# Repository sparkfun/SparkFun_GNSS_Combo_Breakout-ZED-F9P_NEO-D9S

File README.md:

# SparkFun u-blox ZED-F9P NEO-D9S Combo Breakout

<p align="center">

</p>

*[SparkFun u-blox ZED-F9P NEO-D9S Combo Breakout (GPS-22560)](https://www.sparkfun.com/products/22560)*

The [SparkFun u-blox ZED-F9P NEO-D9S Combo Breakout (GPS-22560)](https://www.sparkfun.com/products/22560) combines the u-blox ZED-F9P multi-band high precision GNSS module with the NEO-D9S L-band GNSS correction data receiver. With a clear view of the sky, especially a clear view to the South, this combo breakout will deliver centimeter-level accuracy positioning without needing separate RTK or NTRIP corrections.

The Combo Breakout is designed to work with u-blox's PointPerfect L-band satellite GNSS augmentation service, which provides homogeneous coverage in contiguous USA.

### Important Note:

u-blox provides products and services to "B2B Customers". Only business customers are eligible to register for a Thingstream (PointPerfect) account. You may be required to demonstrate that the use of the combo breakout is in relation to your trade, business, craft or profession. u-blox products and services are not intended for individual consumer use.

## Repository Contents

* **[/docs](/docs/)** - Online documentation files
    * [board_files](/docs/assets/board_files/) - Files for the product design
        * [Eagle design files](https://github.com/sparkfun/SparkFun_GNSS_Combo_Breakout-ZED-F9P_NEO-D9S/blob/main/docs/assets/board_files/ZED-F9P_NEO-D9S_Combo_x02.zip) (.zip)
        * [Schematic](https://github.com/sparkfun/SparkFun_GNSS_Combo_Breakout-ZED-F9P_NEO-D9S/blob/main/docs/assets/board_files/SparkFun_GNSS_Combo_Breakout-ZED-F9P_NEO-D9S_Schematic.pdf) (.pdf)
        * [Dimensions](https://github.com/sparkfun/SparkFun_GNSS_Combo_Breakout-ZED-F9P_NEO-D9S/blob/main/docs/assets/board_files/SparkFun_GNSS_Combo_Breakout-ZED-F9P_NEO-D9S_Dimensions.png) (.png)
* **[/Hardware](/Hardware/)** - Eagle design files (.brd, .sch)

## Documentation

* **[Hookup Guide (mkdocs)](http://docs.sparkfun.com/SparkFun_GNSS_Combo_Breakout-ZED-F9P_NEO-D9S/)** - Hookup guide for the SparkFun u-blox ZED-F9P NEO-D9S Combo Breakout hosted by GitHub pages.

## Product Versions

* [GPS-22560](https://www.sparkfun.com/products/22560) - Initial SparkFun Release

## License Information

This product is _**open source**_! 

Please review the LICENSE.md file for license information. 

If you have any questions or concerns on licensing, please contact technical support on our [SparkFun forums](https://forum.sparkfun.com/viewforum.php?f=152).

Distributed as-is; no warranty is given.

- Your friends at SparkFun.

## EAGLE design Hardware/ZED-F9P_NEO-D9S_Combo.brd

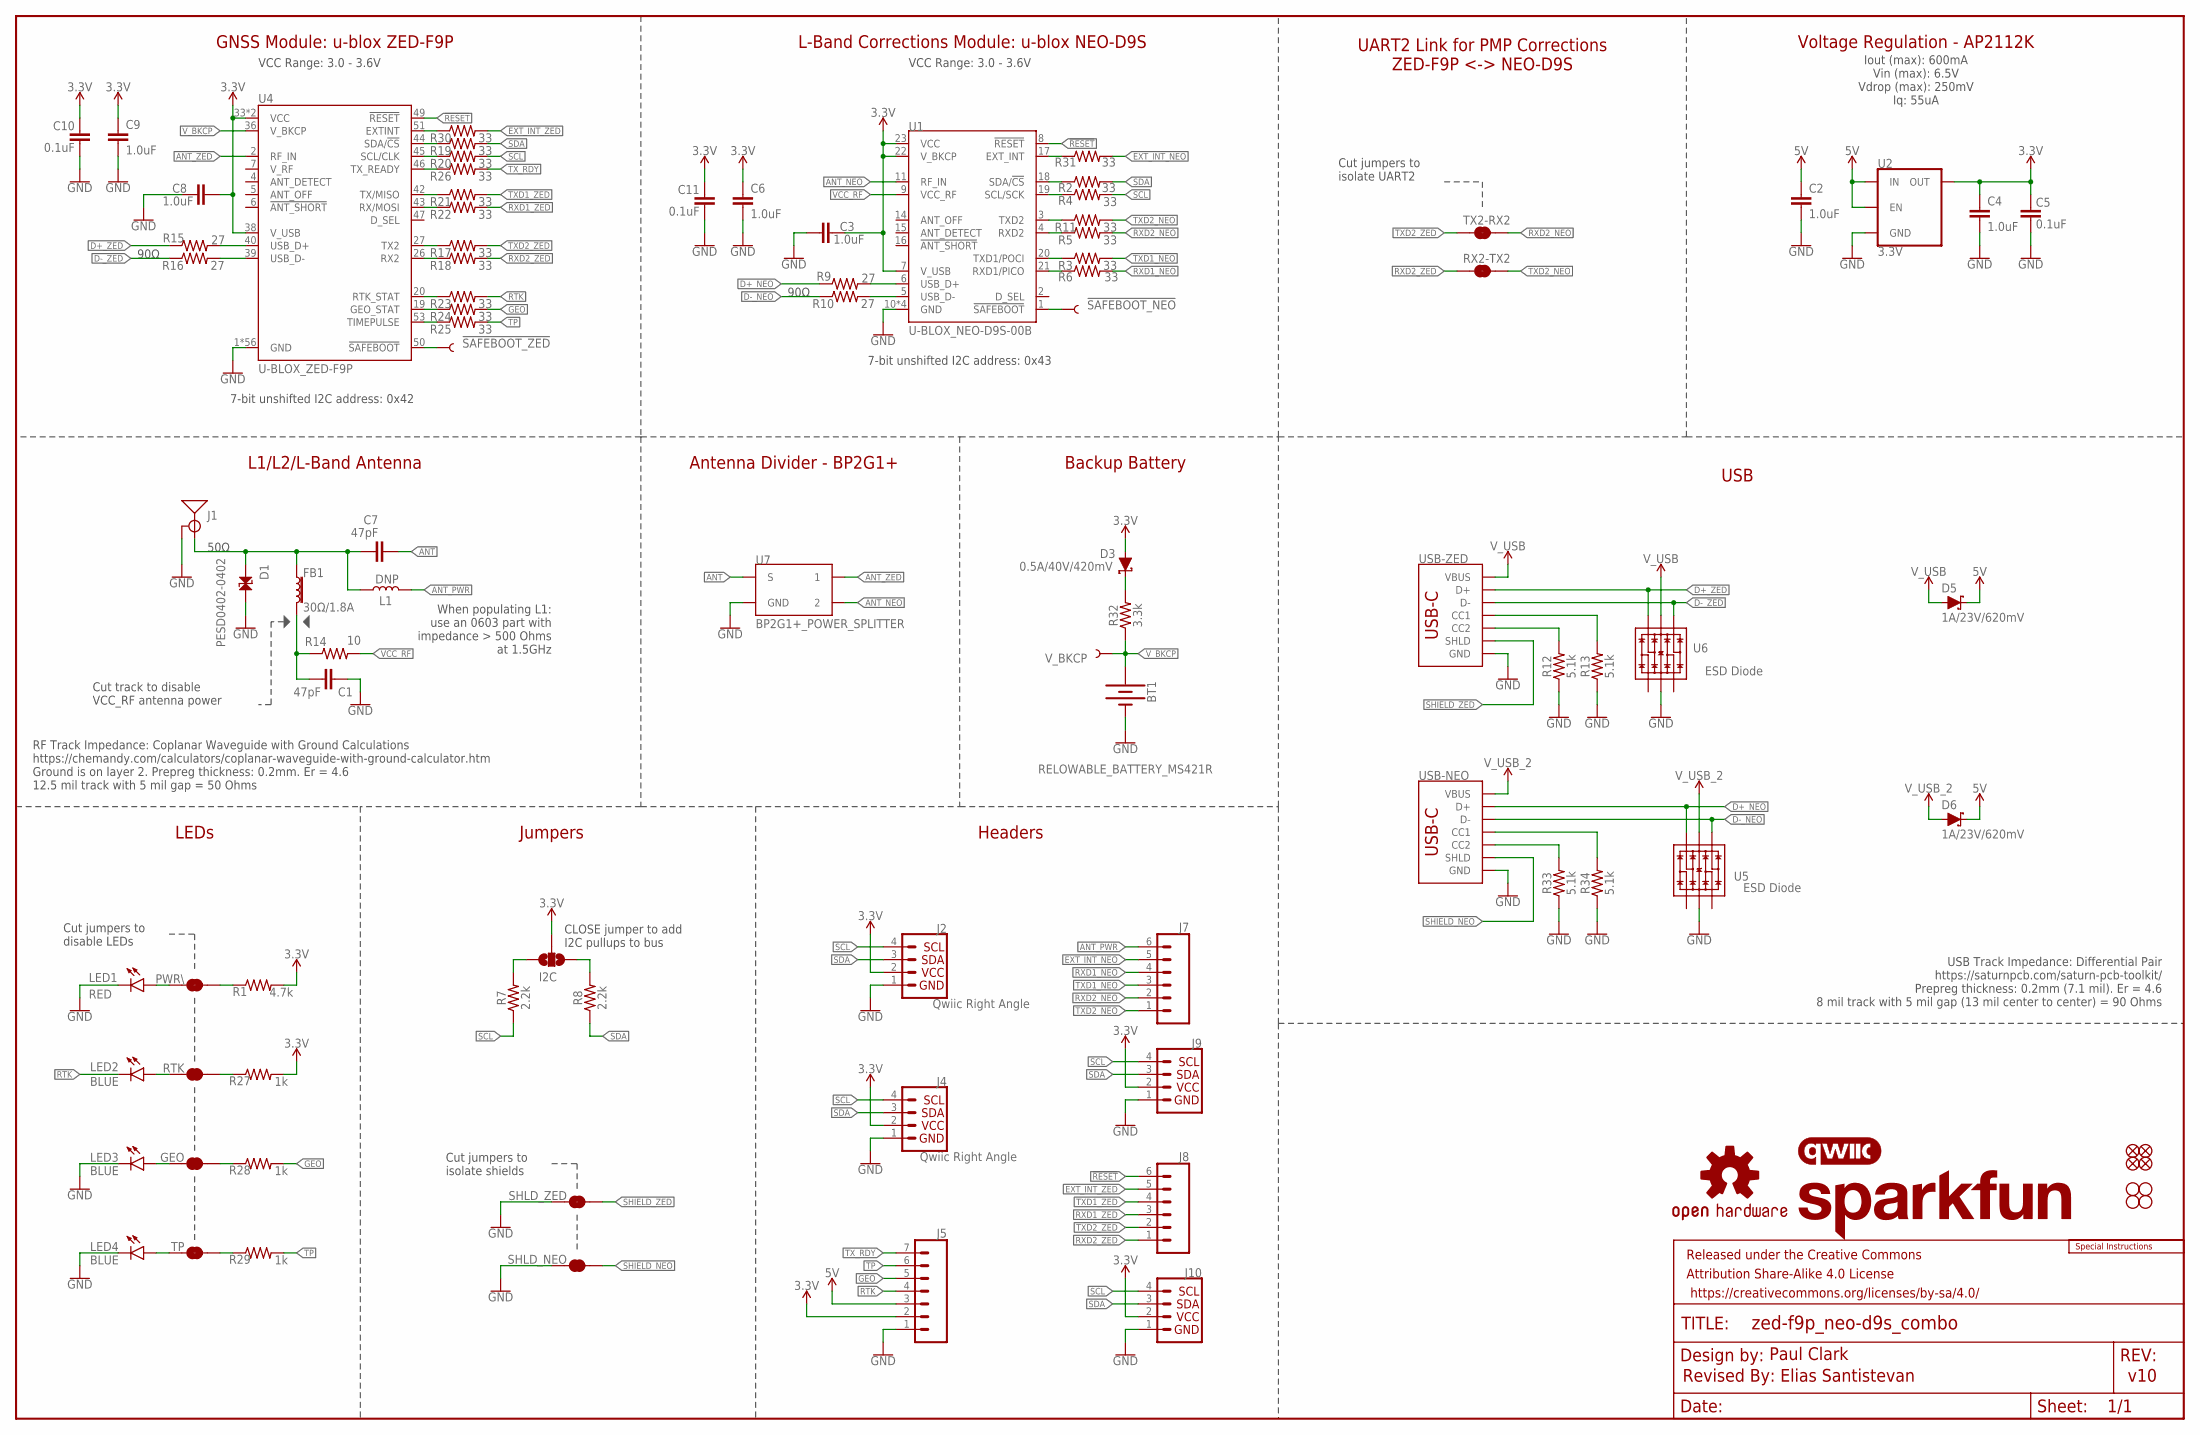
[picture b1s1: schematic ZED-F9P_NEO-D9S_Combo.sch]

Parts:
!SAFEBOOT_NEO!: TEST-POINTPOGO_PTH; 1X01_NO_SILK
!SAFEBOOT_ZED!: TEST-POINTPOGO_PTH; 1X01_NO_SILK
BT1: RELOWABLE_BATTERY_MS421R; MS421R_IV03E
C1, C7: 47pF; 0603
C2, C3, C4, C6, C8, C9: 1.0uF; 0603
C5, C10, C11: 0.1uF; 0603
D1: PESD0402-0402; 0402
D3: 0.5A/40V/420mV; SOD-323
D5, D6: 1A/23V/620mV; SOD-323
FB1: 30Ω/1.8A; 0603
FRAME2: FRAME-LEDGER; CREATIVE_COMMONS
GEO: JUMPER-SMT_2_NC_TRACE_SILK; SMT-JUMPER_2_NC_TRACE_SILK
I2C: JUMPER-SMT_3_NO_SILK; SMT-JUMPER_3_NO_SILK
J1: ANTENNA-SMA-GROUNDEDEDGE_SMA; SMA-EDGE
J2, J4: Qwiic Right Angle; JST04_1MM_RA
J5: CONN_07NO_SILK; 1X07_NO_SILK
J7, J8: CONN_06NO_SILK_NO_POP; 1X06_NO_SILK
J9, J10: I2C_STANDARD_NO_SILK; 1X04_NO_SILK
JP21, JP61, JP71, JP81: FIDUCIALUFIDUCIAL; MICRO-FIDUCIAL
JP31, JP41, JP91, JP101: STAND-OFF
L1: DNP; 0603_NO-CREAM
LED1: RED; LED-0603
LED2, LED3, LED4: BLUE; LED-0603
LOGO2: SFE_LOGO_NAME.1_INCH; SFE_LOGO_NAME_.1
LOGO3: QWIIC_LOGO_5MM; QWIIC_5MM
LOGO4: OSHW-LOGOS; OSHW-LOGO-S
LOGO5: SPECIAL_INSTRUCTIONS-ORDERING; ORDERING_INSTRUCTIONS
PWR\: JUMPER-SMT_2_NC_TRACE_SILK; SMT-JUMPER_2_NC_TRACE_SILK
R1: 4.7k; 0603
R2, R3, R4, R5, R6, R11, R17, R18, R19, R20, R21, R22, R23, R24, R25, R26, R30, R31: 33; 0603
R7, R8: 2.2k; 0603
R9, R10, R15, R16: 27; 0603
R12, R13, R33, R34: 5.1k; 0603
R14: 10; 0603
R27, R28, R29: 1k; 0603
R32: 3.3k; 0603
RTK: JUMPER-SMT_2_NC_TRACE_SILK; SMT-JUMPER_2_NC_TRACE_SILK
RX2-TX2: JUMPER-SMT_2_NC_TRACE_SILK; SMT-JUMPER_2_NC_TRACE_SILK
SHLD_NEO: JUMPER-SMT_2_NC_TRACE_SILK; SMT-JUMPER_2_NC_TRACE_SILK
SHLD_ZED: JUMPER-SMT_2_NC_TRACE_SILK; SMT-JUMPER_2_NC_TRACE_SILK
TP: JUMPER-SMT_2_NC_TRACE_SILK; SMT-JUMPER_2_NC_TRACE_SILK
TX2-RX2: JUMPER-SMT_2_NC_TRACE_SILK; SMT-JUMPER_2_NC_TRACE_SILK
U1: U-BLOX_NEO-D9S-00B; NEO-M9N/M8T/M8U/D9S
U2: 3.3V; SOT23-5
U4: U-BLOX_ZED-F9P; ZED-F9P
U5, U6: ESD Diode; SOT-23-6
U7: BP2G1+_POWER_SPLITTER; XX21
USB-NEO: USB Female Type C Connector; USB-C-16P_4LAYER-PADS
USB-ZED: USB Female Type C Connector; USB-C-16P_4LAYER-PADS
V_BKCP: TEST-POINT3X5; PAD.03X.05

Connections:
3.3V: C3.1, C4.1, C5.2, C6.1, C8.2, C9.1, C10.2, C11.2, D3.A, I2C.2, J2.2, J4.2, J5.2, J9.2, J10.2, R1.2, R27.2, U1.7 (V_USB), U1.22 (V_BKCP), U1.23 (VCC), U2.5 (OUT), U4.33 (VCC), U4.34 (VCC), U4.38 (V_USB)
5V: C2.1, D5.C, D6.C, J5.3, U2.1 (IN), U2.3 (EN)
!RESET!: J8.6, U1.8 (!RESET!), U4.49 (!RESET!)
!SAFEBOOT_NEO!: !SAFEBOOT_NEO!.1, U1.1 (!SAFEBOOT!)
!SAFEBOOT_ZED!: !SAFEBOOT_ZED!.1, U4.50 (!SAFEBOOT!)
ANT: C7.2, U7.2 (S)
ANT_NEO: U1.11 (RF_IN), U7.5 (2)
ANT_PWR: J7.6, L1.2
ANT_VCC: C1.1, FB1.2, R14.1
ANT_ZED: U4.2 (RF_IN), U7.8 (1)
D+_NEO: R9.1, U5.6 (IO4), USB-NEO.A6 (D+), USB-NEO.B6 (D+)
D+_ZED: R15.1, U6.6 (IO4), USB-ZED.A6 (D+), USB-ZED.B6 (D+)
D-_NEO: R10.1, U5.4 (IO3), USB-NEO.A7 (D-), USB-NEO.B7 (D-)
D-_ZED: R16.1, U6.4 (IO3), USB-ZED.A7 (D-), USB-ZED.B7 (D-)
EXT_INT_NEO: J7.5, R31.2
EXT_INT_ZED: J8.5, R30.2
GEO: J5.5, R24.2, R28.2
GND: BT1.-, C1.2, C2.2, C3.2, C4.2, C5.1, C6.2, C8.1, C9.2, C10.1, C11.1, D1.2, J1.GND@0 (GND), J1.GND@1 (GND), J1.GND@2 (GND), J1.GND@3 (GND), J2.1, J4.1, J5.1, J9.1, J10.1, LED1.C, LED3.C, LED4.C, R12.1, R13.1, R33.1, R34.1, SHLD_NEO.1, SHLD_ZED.1, U1.10 (GND), U1.12 (GND), U1.13 (GND), U1.24 (GND), U2.2 (GND), U4.1 (GND), U4.3 (GND), U4.12 (GND), U4.14 (GND), U4.32 (GND), U4.37 (GND), U4.41 (GND), U4.48 (GND), U4.55 (GND), U4.56 (GND), U4.57 (GND), U4.58 (GND), U4.59 (GND), U4.60 (GND), U4.61 (GND), U4.62 (GND), U4.63 (GND), U4.64 (GND), U4.65 (GND), U4.66 (GND), U4.67 (GND), U4.68 (GND), U4.69 (GND), U4.70 (GND), U4.71 (GND), U4.72 (GND), U4.73 (GND), U4.74 (GND), U4.75 (GND), U4.76 (GND), U4.77 (GND), U4.78 (GND), U4.79 (GND), U4.80 (GND), U4.81 (GND), U4.82 (GND), U4.83 (GND), U4.84 (GND), U4.85 (GND), U4.86 (GND), U4.87 (GND), U4.88 (GND), U4.89 (GND), U4.90 (GND), U4.91 (GND), U4.92 (GND), U4.93 (GND), U4.94 (GND), U4.95 (GND), U4.96 (GND), U4.97 (GND), U4.98 (GND), U4.99 (GND), U4.100 (GND), U4.101 (GND), U4.102 (GND), U5.2 (VSS), U6.2 (VSS), U7.1 (GND), U7.3 (GND), U7.4 (GND), U7.6 (GND), U7.7 (GND), USB-NEO.GND, USB-NEO.GND2 (GND), USB-ZED.GND, USB-ZED.GND2 (GND)
unnamed: PWR\.2, R1.1
unnamed: R3.1, U1.20 (TXD1/POCI)
unnamed: R2.1, U1.18 (SDA/!CS!)
unnamed: R4.1, U1.19 (SCL/SCK)
unnamed: I2C.1, R8.2
unnamed: R6.1, U1.21 (RXD1/PICO)
unnamed: R12.2, USB-ZED.B5 (CC2)
unnamed: I2C.3, R7.2
unnamed: R13.2, USB-ZED.A5 (CC1)
unnamed: LED1.A, PWR\.1
unnamed: R9.2, U1.6 (USB_D+)
unnamed: R10.2, U1.5 (USB_D-)
unnamed: D3.C, R32.2
unnamed: R11.1, U1.3 (TXD2)
unnamed: R5.1, U1.4 (RXD2)
unnamed: R15.2, U4.40 (USB_D+)
unnamed: R16.2, U4.39 (USB_D-)
unnamed: R19.1, U4.44 (SDA/!CS!)
unnamed: R20.1, U4.45 (SCL/CLK)
unnamed: R21.1, U4.42 (TX/MISO)
unnamed: R22.1, U4.43 (RX/MOSI)
unnamed: R26.1, U4.46 (TX_READY)
unnamed: LED2.A, RTK.1
unnamed: R17.1, U4.27 (TX2)
unnamed: R18.1, U4.26 (RX2)
unnamed: GEO.1, LED3.A
unnamed: LED4.A, TP.1
unnamed: R27.1, RTK.2
unnamed: GEO.2, R28.1
unnamed: R29.1, TP.2
unnamed: R30.1, U4.51 (EXTINT)
unnamed: R31.1, U1.17 (EXT_INT)
unnamed: R33.2, USB-NEO.B5 (CC2)
unnamed: R34.2, USB-NEO.A5 (CC1)
unnamed: R23.1, U4.20 (RTK_STAT)
unnamed: R24.1, U4.19 (GEO_STAT)
unnamed: R25.1, U4.53 (TIMEPULSE)
RTK: J5.4, LED2.C, R23.2
RXD1_NEO: J7.4, R6.2
RXD1_ZED: J8.3, R22.2
RXD2_NEO: J7.2, R5.2, TX2-RX2.2
RXD2_ZED: J8.1, R18.2, RX2-TX2.1
SCL: J2.4, J4.4, J9.4, J10.4, R4.2, R7.1, R20.2
SDA: J2.3, J4.3, J9.3, J10.3, R2.2, R8.1, R19.2
SHIELD_NEO: SHLD_NEO.2, USB-NEO.SHLD1 (SHLD), USB-NEO.SHLD2 (SHLD), USB-NEO.SHLD3 (SHLD), USB-NEO.SHLD4 (SHLD)
SHIELD_ZED: SHLD_ZED.2, USB-ZED.SHLD1 (SHLD), USB-ZED.SHLD2 (SHLD), USB-ZED.SHLD3 (SHLD), USB-ZED.SHLD4 (SHLD)
SMA: C7.1, D1.1, FB1.1, J1.SIG (SIGNAL), L1.1
TP: J5.6, R25.2, R29.2
TXD1_NEO: J7.3, R3.2
TXD1_ZED: J8.4, R21.2
TXD2_NEO: J7.1, R11.2, RX2-TX2.2
TXD2_ZED: J8.2, R17.2, TX2-RX2.1
TX_RDY: J5.7, R26.2
VCC_RF: R14.2, U1.9 (VCC_RF)
V_BKCP: BT1.+, R32.1, U4.36 (V_BKCP), V_BKCP.1
V_USB: D5.A, U6.5 (VCC), USB-ZED.VBUS1 (VBUS), USB-ZED.VBUS2 (VBUS)
V_USB_2: D6.A, U5.5 (VCC), USB-NEO.VBUS1 (VBUS), USB-NEO.VBUS2 (VBUS)

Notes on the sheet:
v10
7-bit unshifted I2C address: 0x43
CLOSE jumper to add I2C pullups to bus
Cut jumpers to disable LEDs
Paul Clark
Headers
LEDs
L-Band Corrections Module: u-blox NEO-D9S
L1/L2/L-Band Antenna
USB
VCC Range: 3.0 - 3.6V
Cut jumpers to isolate shields
50Ω
Cut track to disable VCC_RF antenna power
90Ω
When populating L1: use an 0603 part with impedance > 500 Ohms at 1.5GHz
Iout (max): 600mA Vin (max): 6.5V Vdrop (max): 250mV Iq: 55uA
7-bit unshifted I2C address: 0x42
GNSS Module: u-blox ZED-F9P
Antenna Divider - BP2G1+
Jumpers
Backup Battery
Cut jumpers to isolate UART2
Voltage Regulation - AP2112K
RF Track Impedance: Coplanar Waveguide with Ground Calculations https://chemandy.com/calculators/coplanar-waveguide-with-ground-calculator.htm Ground is on layer 2. Prepreg thickness: 0.2mm. Er = 4.6 12.5 mil track with 5 mil gap = 50 Ohms
UART2 Link for PMP Corrections ZED-F9P <-> NEO-D9S
Revised By: Elias Santistevan
USB Track Impedance: Differential Pair https://saturnpcb.com/saturn-pcb-toolkit/ Prepreg thickness: 0.2mm (7.1 mil). Er = 4.6 8 mil track with 5 mil gap (13 mil center to center) = 90 Ohms

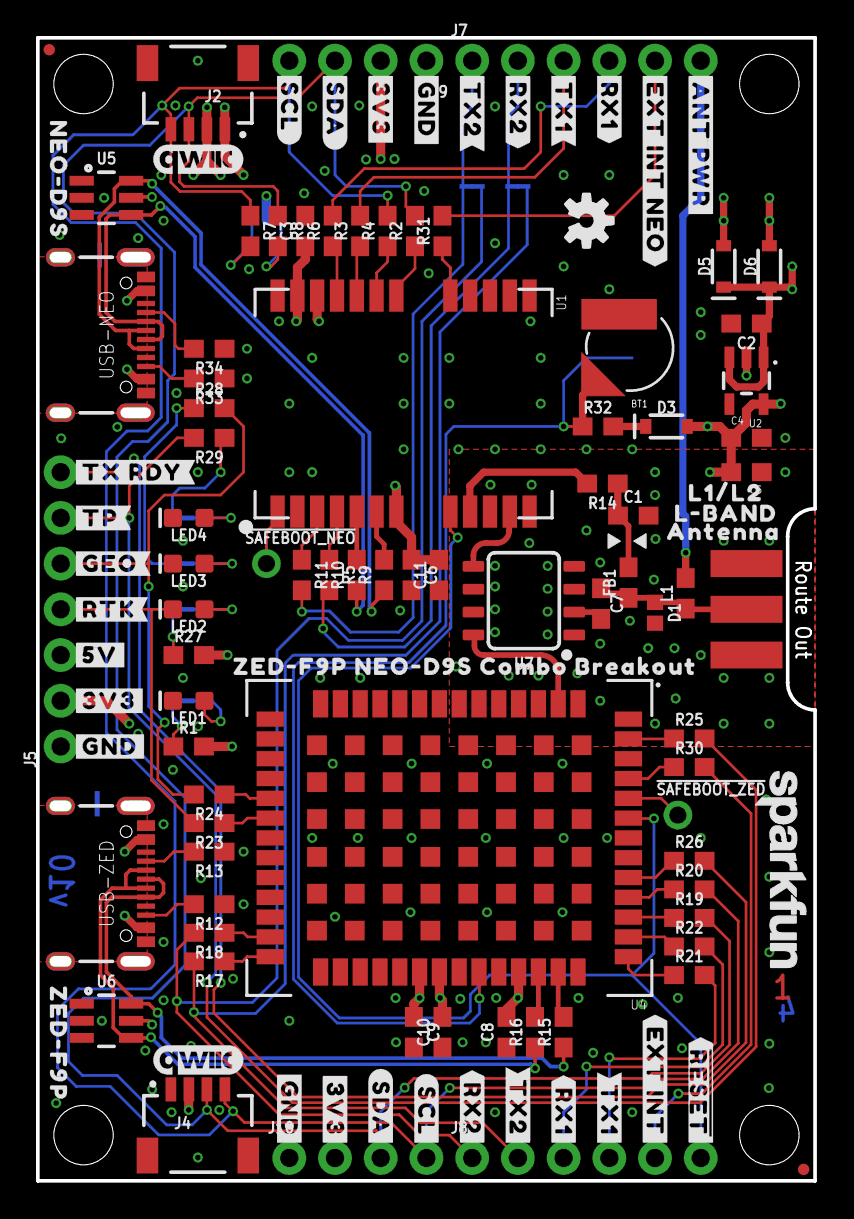
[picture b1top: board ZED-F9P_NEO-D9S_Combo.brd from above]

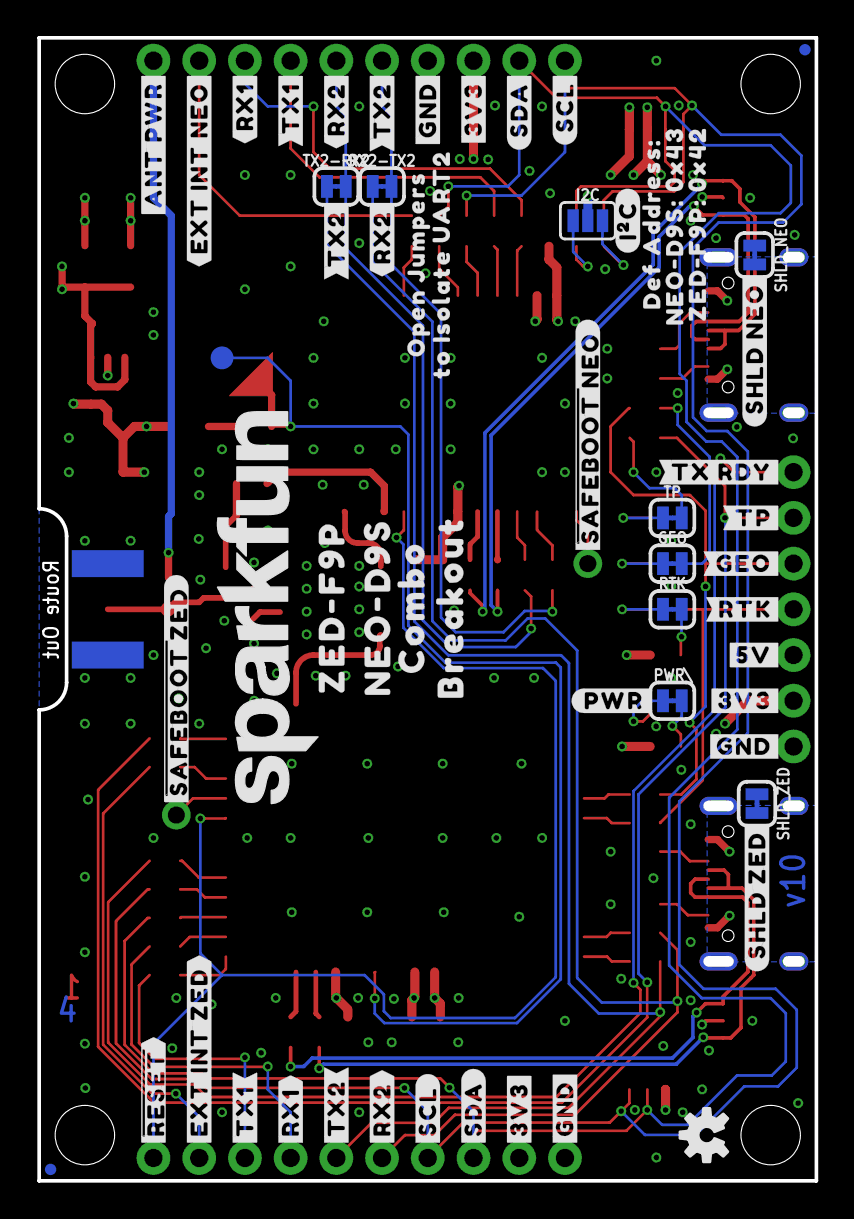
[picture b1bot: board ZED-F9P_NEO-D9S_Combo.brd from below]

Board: 4 copper layers, 43.2 x 63.5 mm, 179 parts (60 on the bottom side), 75 nets.

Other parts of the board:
LOGO1: OSHW-LOGOS; OSHW-LOGO-S
LOGO6: QWIIC_LOGO_5MM; QWIIC_5MM
U$1, U$2, U$3: #GND#0
U$4, U$5, U$6: #GND#1
U$7: #SHLD_ZED#15
U$8, U$10: #SDA#0
U$9, U$13: #SCL#0
U$11, U$12: #SDA#1
U$14: L#BAND18
U$15, U$30: #SCL#1
U$16: #RTK#0
U$17: #RTK#1
U$18: #GEO#0
U$19: #GEO#1
U$20: #5V#0
U$21: #5V#6
U$22, U$23, U$56: #3V3#0
U$24, U$25, U$70: #3V3#4
U$26: #TP#0
U$27: #TP#1
U$28: #TX_RDY#0
U$29: #TX_RDY#1
U$31, U$39, U$40: #TX2#0
U$32, U$34, U$35: #RX2#0
U$33: L1#L218
U$36, U$37: #RX2#3
U$41, U$42: #TX2#3
U$43, U$44: #RX1#0
U$45: ##RESET##0
U$46: ##RESET##1
U$47: #EXT_INT#0
U$48: #EXT_INT_ZED#0
U$49, U$50: #RX1#2
U$51, U$57: #TX1#0
U$52: #I�C#0
U$53: #SHLD_NEO#12
U$54: ANTENNA18
U$55: NEO#D9S16
U$58: #ANT_PWR#0
U$59: #ANT_PWR#1
U$60, U$61: #TX1#2
U$62: #EXT_INT_NEO#0
U$63: #EXT_INT_NEO#1
U$64: COMBO16
U$65: ZED#F9P10
U$66: NEO#D9S10
U$67: BREAKOUT17
U$68: SFE_LOGO_NAME_.2
U$69: #PWR#0
U$71: ##SAFEBOOT#_NEO#13
U$72: ##SAFEBOOT#_ZED#14
U$73: OPEN_JUMPERS13
U$74: TO_ISOLATE_UART214
U$75: ZED#F9P_NEO#D9S_COMBO_BREAKOUT0
U$76: DEF_ADDRESS#_12
U$78: ZED#F9P16
U$79: NEO#D9S#13
U$80: ZED#F9P#13
U$81: 0X4313
U$82: 0X4213

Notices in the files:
README.md:
License: CC BY-SA 4.0
parts and their libraries:
SparkFun-Resistors: Licensing: Creative Commons ShareAlike 4.0 International - https://creativecommons.org/licenses/by-sa/4.0
SparkFun-Aesthetics: Released under the Creative Commons Attribution Share-Alike 4.0 License
SparkFun-Aesthetics: https://creativecommons.org/licenses/by-sa/4.0
